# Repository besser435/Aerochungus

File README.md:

# Aerochungus
 Rocket flight computers and data recorders.

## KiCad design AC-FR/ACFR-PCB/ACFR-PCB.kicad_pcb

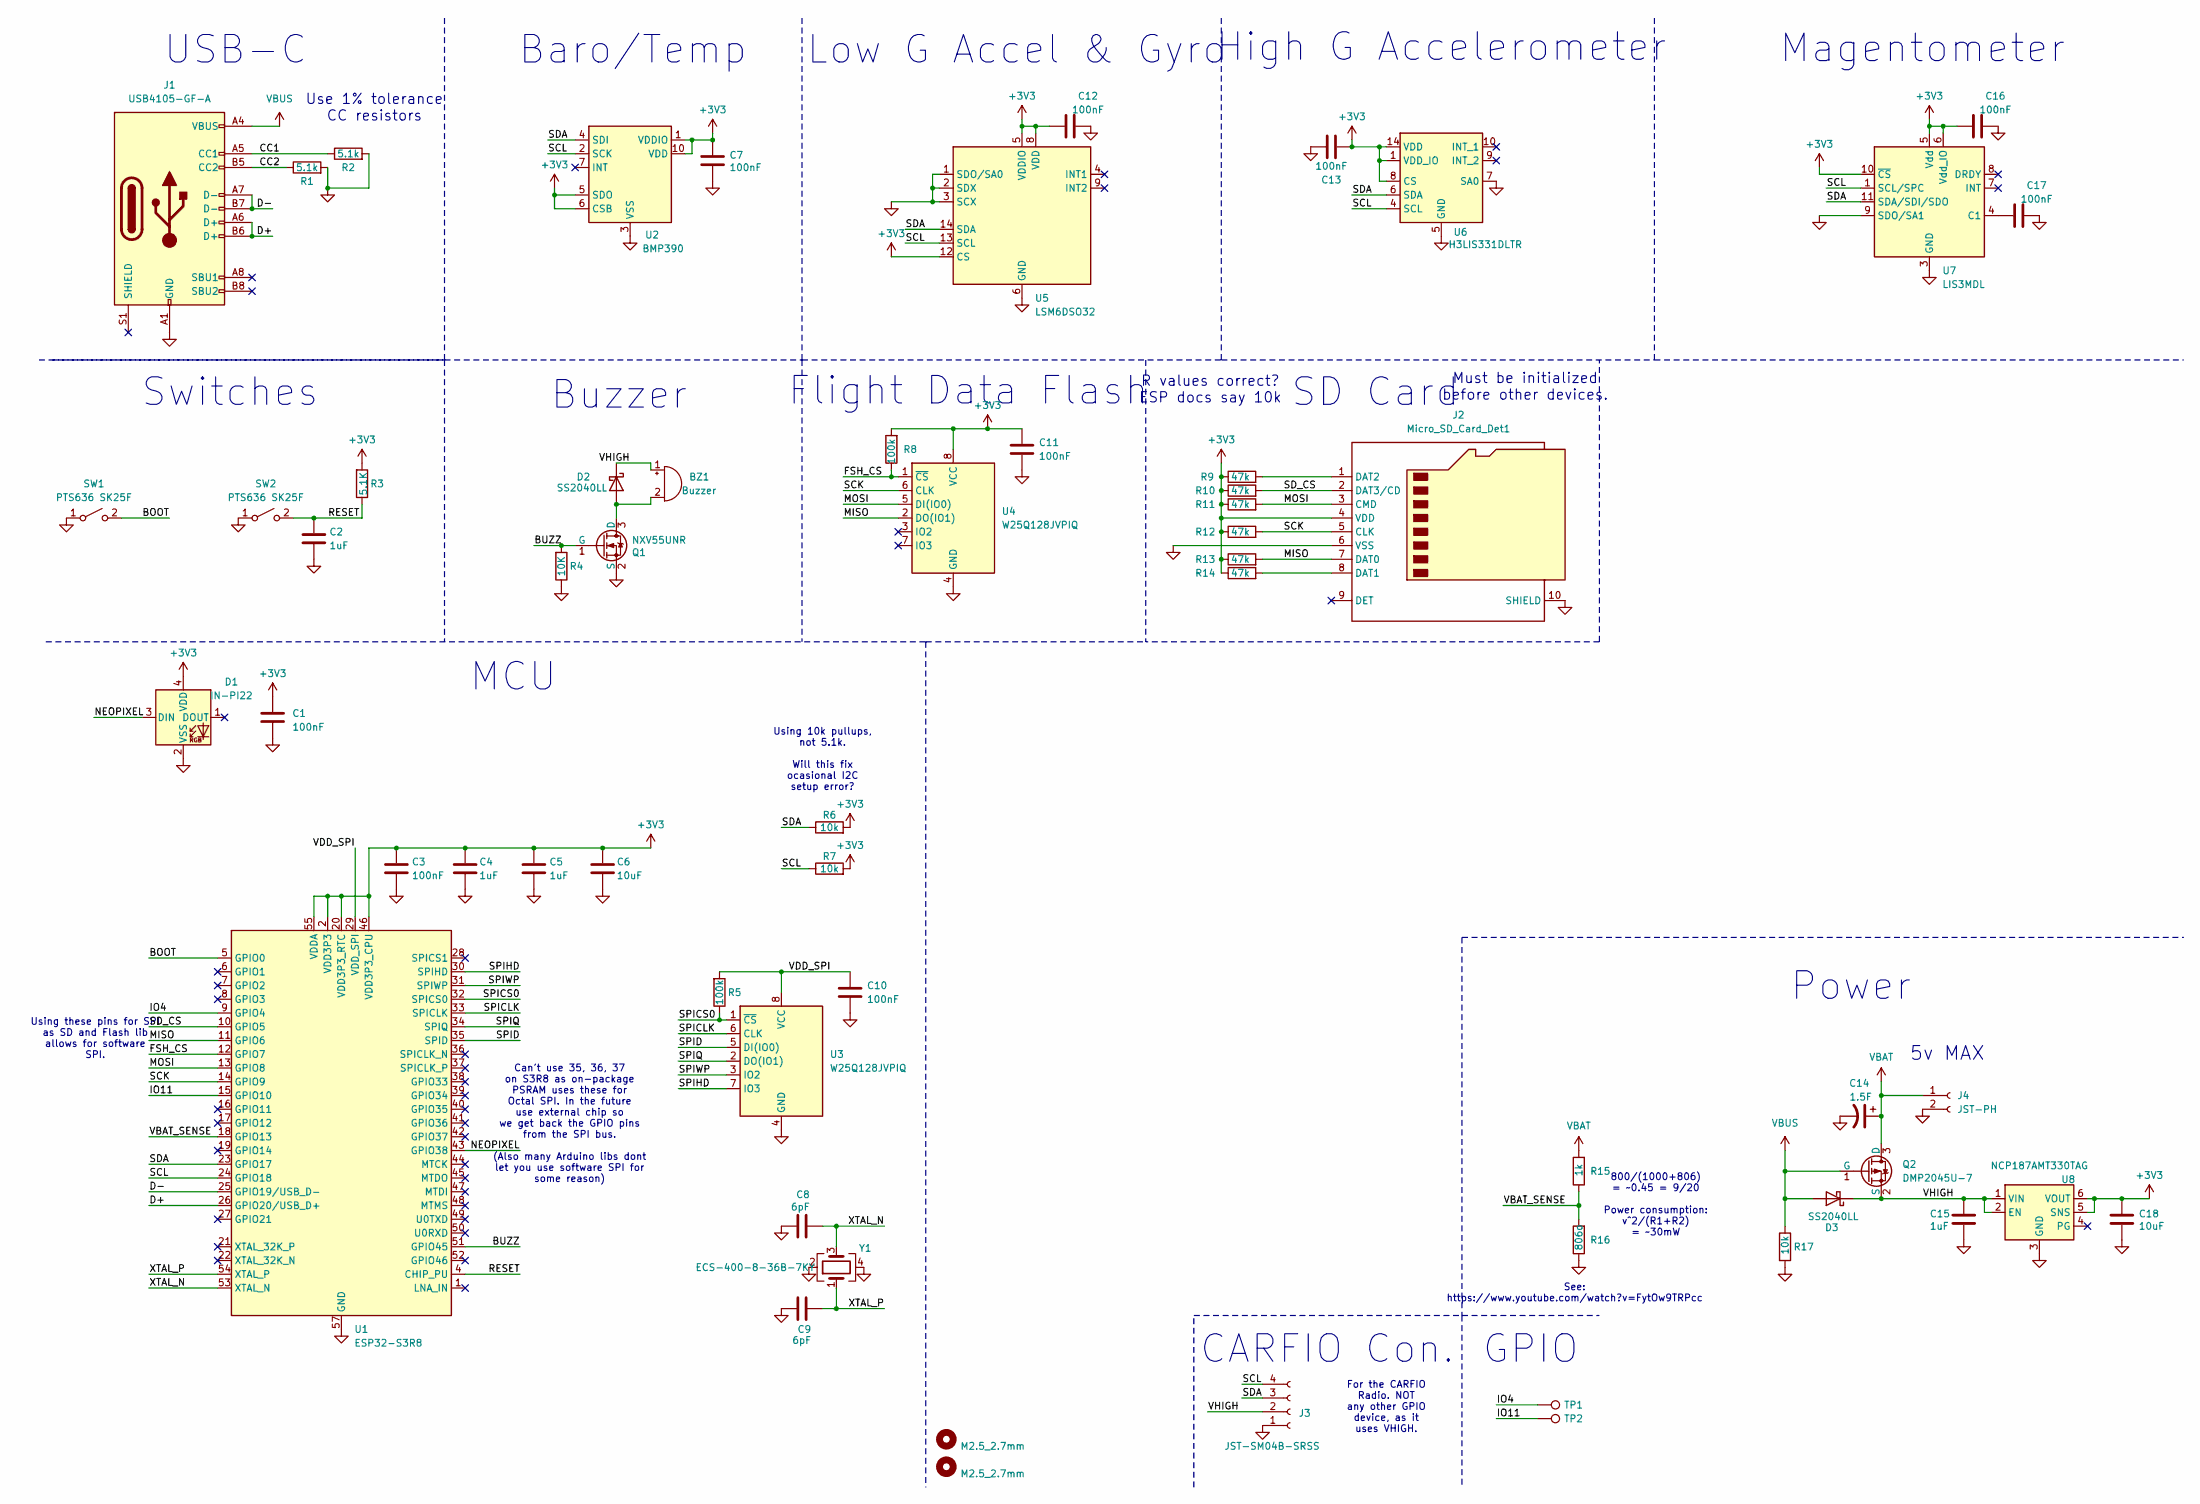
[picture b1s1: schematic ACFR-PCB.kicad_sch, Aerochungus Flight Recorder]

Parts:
BZ1: Buzzer; CMT-9504-87-SMT_BUZZER
C1, C3, C7, C10, C11, C12, C13, C16, C17: 100nF; C_0603_1608Metric
C2, C4, C5, C15: 1uF; C_0603_1608Metric
C6, C18: 10uF; C_0603_1608Metric
C8, C9: 6pF; C_0402_1005Metric
C14: 1.5F; CP_Radial_D16.5mm_P12mm
D1: IN-PI22; IN-PI22TAT5R5G5B
D2, D3: SS2040LL; D_SOD-123
H1, H2: M2.5_2.7mm; M2.5_2.7mm_hole
J1: USB4105-GF-A; USB_C_Receptacle_GCT_USB4105-xx-A_16P_TopMnt_Horizontal
J2: Micro_SD_Card_Det1; GCT_MEM2061-01-188-00-A_REVA
J3: JST-SM04B-SRSS; JST_SH_SM04B-SRSS-TB_1x04-1MP_P1.00mm_Horizontal
J4: JST-PH; JST_PH_S2B-PH-SM4-TB_1x02-1MP_P2.00mm_Horizontal
Q1: NXV55UNR; SOT-23-3
Q2: DMP2045U-7; SOT-23-3
R1, R2: 5.1k; C_0603_1608Metric
R3: 5.1K; C_0603_1608Metric
R4: 10K; C_0603_1608Metric
R5, R8: 100k; C_0603_1608Metric
R6, R7, R17: 10k; C_0603_1608Metric
R9, R10, R11, R12, R13, R14: 47k; C_0603_1608Metric
R15: 1k; C_0603_1608Metric
R16: 806o; C_0603_1608Metric
SW1, SW2: PTS636 SK25F; SW_Tactile_SPST_NO_Straight_CK_PTS636Sx25SMTRLFS
TP1, TP2: TestPoint; TestPoint_Pad_1.0x1.0mm
U1: ESP32-S3R8; QFN-56-1EP_7x7mm_P0.4mm_EP4x4mm
U2: BMP390; 10-WFLGA
U3, U4: W25Q128JVPIQ; WSON-8-1EP_6x5mm_P1.27mm_EP3.4x4.3mm
U5: LSM6DSO32; LGA-14_3x2.5mm_P0.5mm_LayoutBorder3x4y
U6: H3LIS331DLTR; TLGA-16L
U7: LIS3MDL; LGA-12_2x2mm_P0.5mm
U8: NCP187AMT330TAG; 6-WDFN_2x2mm_EP
Y1: ECS-400-8-36B-7KY; Crystal_SMD_EuroQuartz_X22-4Pin_2.5x2.0mm

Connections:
+3V3: C1.1, C3.1, C4.1, C5.1, C6.1, C7.2, C11.1, C12.1, C13.1, C16.1, C18.2, D1.4 (VDD), J2.4 (VDD), R3.2, R6.2, R7.2, R8.2, R9.1, R10.1, R11.1, R12.1, R13.1, R14.1, U1.2 (VDD3P3), U1.3 (VDD3P3), U1.20 (VDD3P3_RTC), U1.46 (VDD3P3_CPU), U1.55 (VDDA), U1.56 (VDDA), U2.1 (VDDIO), U2.5 (SDO), U2.6 (CSB), U2.10 (VDD), U4.8 (VCC), U5.5 (VDDIO), U5.8 (VDD), U5.12 (CS), U6.1 (VDD_IO), U6.8 (CS), U6.14 (VDD), U6.15 (NC), U7.5 (Vdd), U7.6 (Vdd_IO), U7.10 (~CS), U8.5 (SNS), U8.6 (VOUT)
/BOOT: SW1.2 (B), U1.5 (GPIO0)
/BUZZ: Q1.1 (G), R4.2, U1.51 (GPIO45)
/CC1: J1.A5 (CC1), R2.1
/CC2: J1.B5 (CC2), R1.1
/D+: J1.A6 (D+), J1.B6 (D+), U1.26 (GPIO20/USB_D+)
/D-: J1.A7 (D-), J1.B7 (D-), U1.25 (GPIO19/USB_D-)
/FSH_CS: R8.1, U1.12 (GPIO7), U4.1 (~CS)
/IO4: TP1.1, U1.9 (GPIO4)
/IO11: TP2.1, U1.15 (GPIO10)
/MISO: J2.7 (DAT0), R13.2, U1.11 (GPIO6), U4.2 (DO(IO1))
/MOSI: J2.3 (CMD), R11.2, U1.13 (GPIO8), U4.5 (DI(IO0))
/NEOPIXEL: D1.3 (DIN), U1.43 (GPIO38)
/RESET: C2.1, R3.1, SW2.2 (B), U1.4 (CHIP_PU)
/SCK: J2.5 (CLK), R12.2, U1.14 (GPIO9), U4.6 (CLK)
/SCL: J3.4, R7.1, U1.24 (GPIO18), U2.2 (SCK), U5.13 (SCL), U6.4 (SCL), U7.1 (SCL/SPC)
/SDA: J3.3, R6.1, U1.23 (GPIO17), U2.4 (SDI), U5.14 (SDA), U6.6 (SDA), U7.11 (SDA/SDI/SDO)
/SD_CS: J2.2 (DAT3/CD), R10.2, U1.10 (GPIO5)
/SPICLK: U1.33 (SPICLK), U3.6 (CLK)
/SPICS0: R5.1, U1.32 (SPICS0), U3.1 (~CS)
/SPID: U1.35 (SPID), U3.5 (DI(IO0))
/SPIHD: U1.30 (SPIHD), U3.7 (IO3)
/SPIQ: U1.34 (SPIQ), U3.2 (DO(IO1))
/SPIWP: U1.31 (SPIWP), U3.3 (IO2)
/VBAT_SENSE: R15.1, R16.2, U1.18 (GPIO13)
/VDD_SPI: C10.1, R5.2, U1.29 (VDD_SPI), U3.8 (VCC)
/VHIGH: BZ1.1 (+), C15.2, D2.1 (K), D3.1 (K), J3.2, Q2.2 (S), U8.1 (VIN), U8.2 (EN)
/XTAL_N: C8.2, U1.53 (XTAL_N), Y1.3
/XTAL_P: C9.1, U1.54 (XTAL_P), Y1.1
GND: C1.2, C2.2, C3.2, C4.2, C5.2, C6.2, C7.1, C8.1, C9.2, C10.2, C11.2, C12.2, C13.2, C14.2, C15.1, C16.2, C17.2, C18.1, D1.2 (VSS), J1.A1 (GND), J1.A12 (GND), J1.B1 (GND), J1.B12 (GND), J2.6 (VSS), J2.10 (SHIELD), J3.1, J4.2, Q1.2 (S), R1.2, R2.2, R4.1, R16.1, R17.2, SW1.1 (A), SW2.1 (A), U1.57 (GND), U2.3 (VSS), U2.8 (VSS), U2.9 (VSS), U3.4 (GND), U4.4 (GND), U5.1 (SDO/SA0), U5.2 (SDX), U5.3 (SCX), U5.6 (GND), U5.7 (GND), U6.5 (GND), U6.7 (SA0), U6.10 (NC), U6.12 (GND), U6.13 (GND), U6.16 (GND), U7.2 (GND), U7.3 (GND), U7.9 (SDO/SA1), U7.12 (GND), U8.3 (GND), U8.EP, Y1.2, Y1.4
unnamed: BZ1.2 (-), D2.2 (A), Q1.3 (D)
unnamed: J2.8 (DAT1), R14.2
unnamed: J2.1 (DAT2), R9.2
unnamed: C17.1, U7.4 (C1)
VBAT: C14.1, J4.1, Q2.3 (D), R15.2
VBUS: D3.2 (A), J1.A4 (VBUS), J1.A9 (VBUS), J1.B4 (VBUS), J1.B9 (VBUS), Q2.1 (G), R17.1

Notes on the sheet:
GPIO
Baro/Temp
Switches
Low G Accel & Gyro
Use 1% tolerance CC resistors
800/(1000+806) = ~0.45 = 9/20 Power consumption: v^2/(R1+R2) = ~30mW
Flight Data Flash
SD Card
5v MAX
MCU
Power
Using these pins for SPI as SD and Flash lib allows for software SPI.
CARFIO Con.
USB-C
R values correct? ESP docs say 10k
For the CARFIO Radio. NOT any other GPIO device, as it uses VHIGH.
See: https://www.youtube.com/watch?v=FytOw9TRPcc
Must be initialized before other devices.
High G Accelerometer
Using 10k pullups, not 5.1k. Will this fix ocasional I2C setup error?
Magentometer
Can't use 35, 36, 37 on S3R8 as on-package PSRAM uses these for Octal SPI. In the future use external chip so we get back the GPIO pins from the SPI bus. (Also many Arduino libs dont let you use software SPI for some reason)
Buzzer

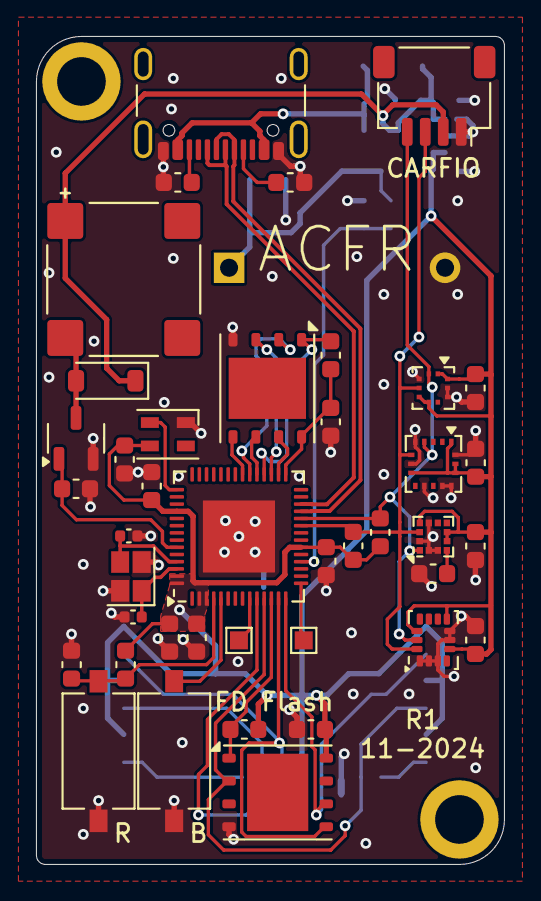
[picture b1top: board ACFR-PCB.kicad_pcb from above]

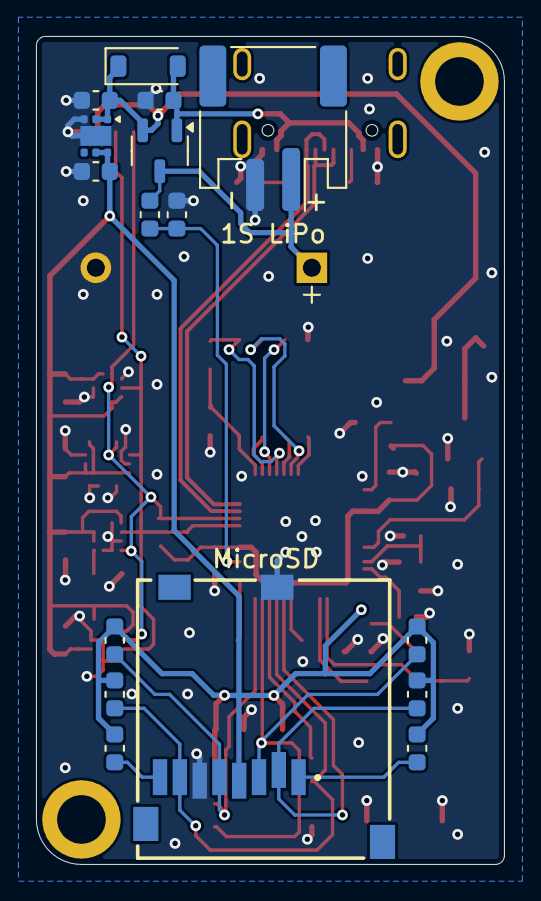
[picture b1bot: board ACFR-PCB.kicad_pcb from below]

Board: 4 copper layers, 26.0 x 46.0 mm, 60 parts (17 on the bottom side), 36 nets.

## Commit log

2024-09-07 Start on ACFR schematic
2024-10-06 Add High G Accel, clean schematic
2024-10-06 i forgor
2024-10-10 Change to IMU, start on buzzer, add magnetometer
2024-10-16 Start on software
2024-10-23 Add Flash and SD card SPI stuff
2024-10-25 do the shitfuck
2024-10-27 Finalize Schematic
2024-10-27 Add batt voltage helper
2024-10-30 Tune schematic, start on PCB for eel on cod
2024-10-31 Redo power
2024-11-02 why do the colors not not stay after a crash this was supposed to be fixed in fucking 8.0.2
2024-11-02 Finalize part placement
2024-11-02 Start on routing (kill the project, its horrible)
2024-11-03 Finally make progress on layout and routing
2024-11-03 Work on routing
2024-11-03 Continue work on routing
2024-11-07 ACFR R1
2025-01-26 stuff
